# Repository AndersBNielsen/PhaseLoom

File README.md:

# PhaseLoom

PhaseLoom is a unique Software Defined Radio (SDR) frontend built around the legendary MOS Technology 6502 CPU, celebrating its 50th anniversary. This project combines classic computing with modern SDR techniques, offering a hands-on platform for radio experimentation and development.
Update: The PhaseLoom now has a companion ADC board with antialiasing filter, the [PhaseLatch Mini](https://github.com/AndersBNielsen/PhaseLatchMini)!

## Purchase

Interested in owning a PhaseLoom?  
[Buy one here](https://www.imania.dk/index.php?cPath=204&sort=5a&language=en).

## Project Story & Background
Hello everyone!
I just made the coolest gadget of the year. It’s a Software Defined Radio based on the MOS Technology 6502 CPU, which powered the Apple I & II, Commodore computers, NES, Ataris, and more. This year marks its 50th anniversary!

SDRs are the Swiss Army Knives of radio frequencies. Instead of purpose-built hardware for each use case, SDRs use software to handle filtering and demodulation, making them flexible and upgradable. With PhaseLoom, you get a 6502-based SDR platform—yes, a 6502 SDR!—that lets you experiment with radio signals, decode transponders, listen to shortwave, and more.

The PhaseLoom is designed as an Arduino-style shield for the 65uino, the smallest of my 6502-based computers. It features a Quadrature Sampling Detector, Phase Locked Loop LO Synthesizer, and SDR frontend. The project is open source, and all hardware files, schematics, and source code are available for you to use and modify.

## Features
- KiCad PCB and schematic files
- Gerber files for manufacturing
- Bill of Materials (BOM) and Component Placement List (CPL)
- Images of PCB versions and layouts
- Excel sheet for SI5351 PLL calculations
- Arduino shield form factor for easy integration
- Compatible with 6502, Arduino, ESP32, and other i2c-capable boards

## Technical Highlights
- Quadrature Sampling Detector using Tayloe-style commutating mixers
- SI5351 clock generator for flexible LO generation
- Differential signal processing for improved noise immunity
- Designed for direct conversion SDR and future expansion
- Open source 6502 assembly library for SI5351 control

## Folder Structure
- `PhaseLoom.kicad_pcb` / `PhaseLoom.kicad_sch`: Main PCB and schematic files
- `images/`: Photos and renders of PCB versions
- `jlcpcb/`: Manufacturing files for JLCPCB
  - `gerber/`: Gerber files for PCB fabrication
- `GRC/`: GNU Radio Companion flowgraphs
  - `Aliasing_example.grc`: Demonstrates aliasing effects and IQ sampling
  - `PhaseLoom.grc`: Flowgraph for PhaseLoom SDR frontend
- `PhaseLoom-backups/`: Backup archives of project versions
- `SI5351_PLL_Calc_Formulas.xlsx`: PLL calculation formulas

## How to Use
[6502 source code still lives over on the 65uino project](https://github.com/AndersBNielsen/65uino/)

The main 65uino firmware currently comes with support for the PhaseLoom built in. Assemble a recent binary and you're good to go. 

The 65uino automatically detects the si5351 and goes into SDR mode, that let's you use the buttons and LED's on the PhaseLoom to tune the channels. 

Leftmost button(1): Channel down
Second button: Unused
Third button: Unused
Fourth button: Channel up
Rightmost button: Tune to selected channel.

LED's show the current channel as a binary count. 

To change the available channels update the source code using the Excel spreadsheet to get new byte values for the lookup tables - let me know if you'd like to see a video about that. 

## Other host hardware?
Want to use the PhaseLoom with something that's not a 6502 computer? Go right ahead and use it with anything that does i2c - even better something that already has an si5351 library. 

## Images
Find PCB photos and renders in the `images/` folder for reference and documentation.

## Getting a PCB

## Production & Manufacturing
- The `jlcpcb/gerber/` folder contains all necessary files for PCB fabrication.
- The `production_files/` folder includes:
  - `BOM-PhaseLoom.csv`: Bill of Materials
  - `CPL-PhaseLoom.csv`: Component Placement List
  - `GERBER-PhaseLoom.zip`: Zipped Gerber files for easy upload

This project is kindly sponsored by JLCPCB. They offer cheap, professional looking PCBs and super fast delivery.

Step 1: Get the gerber file zip package from the /hardware folder

Step 2: Upload to JLCPCB [https://jlcpcb.com/?from=Anders_N](https://jlcpcb.com/?from=Anders_N)

Step 3: Pick your color, surface finish and order.

You can use these affiliate links to get a board for $2 and also get $54 worth of New User Coupons at: https://jlcpcb.com/?from=Anders_N

And in case you also want to order a 3D-printed case you can use this link. 
How to Get a $7 3D Printing Coupon: [https://3d.jlcpcb.com/?from=Anders3DP](https://jlc3dp.com/?from=Anders_N)

---

For more details, technical explanations, and the full story behind PhaseLoom, check out the project video and documentation. Special thanks to JLCPCB and Fnirsi for supporting the development of this project!

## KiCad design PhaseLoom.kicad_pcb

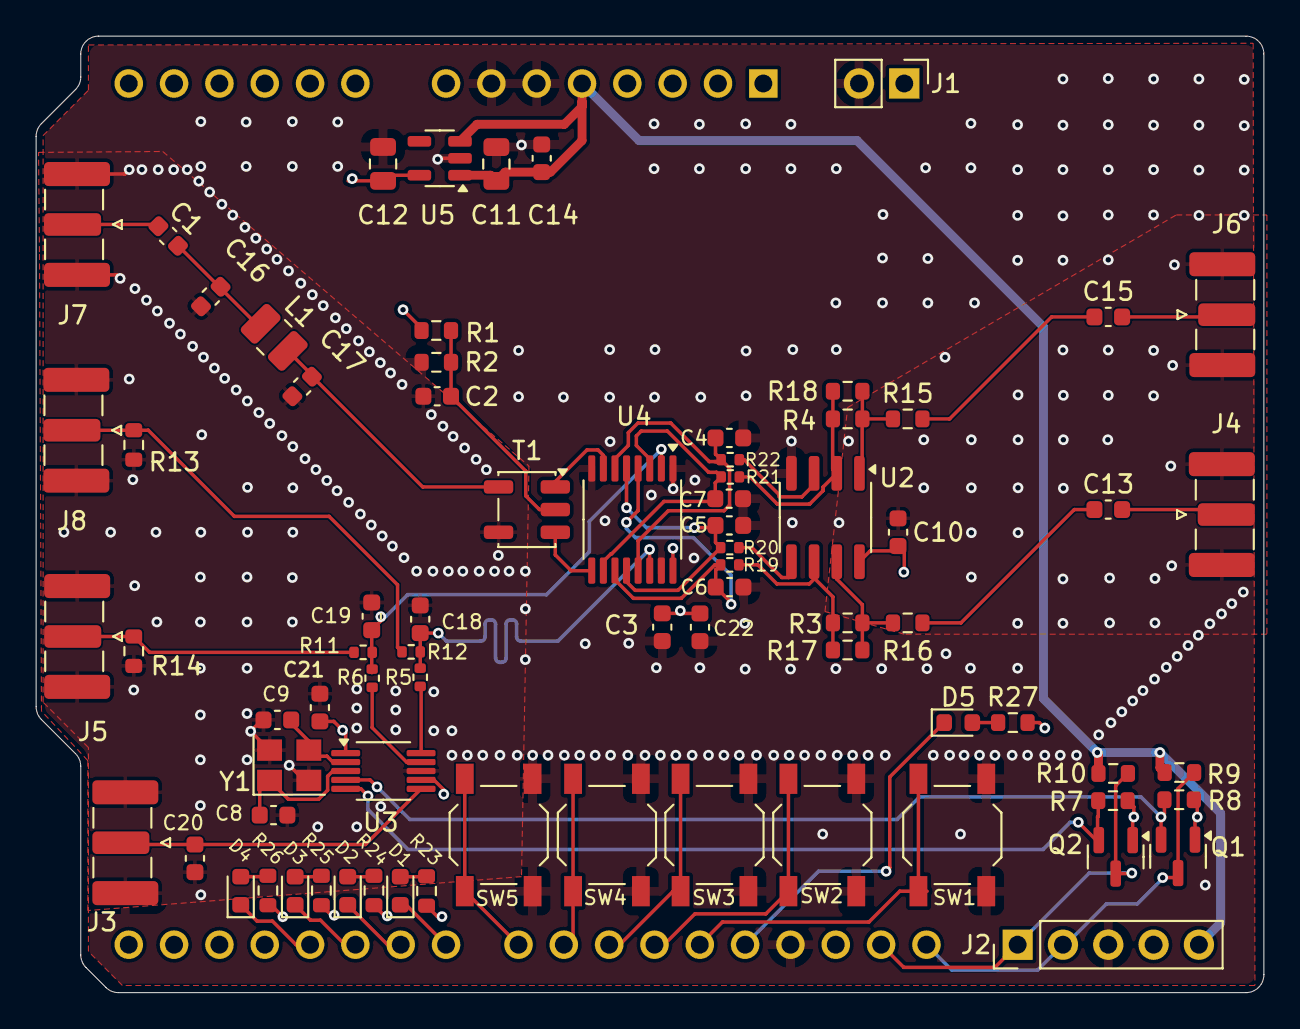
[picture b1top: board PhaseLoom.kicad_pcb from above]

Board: 4 copper layers, 68.8 x 53.6 mm, 77 parts (1 on the bottom side), 51 nets.

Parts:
A1: Arduino_UNO_R3
C1, C10, C21, C22: 100nF; C_0603_1608Metric
C2, C3, C13, C14, C15: 10uF; C_0603_1608Metric
C4, C5, C6, C7: 1nF; C_0603_1608Metric
C8, C9: 2pF; C_0603_1608Metric
C11, C12: 1uF; C_0805_2012Metric
C16, C17: 18pF; C_0603_1608Metric
C18, C19, C20: NC; C_0603_1608Metric
D1, D2, D3, D4, D5: RED; LED_0603_1608Metric
J1: NC; PinHeader_1x02_P2.54mm_Vertical
J2: NC; PinHeader_1x05_P2.54mm_Vertical
J3: CLK2; SMA_Samtec_SMA-J-P-H-ST-EM1_EdgeMount
J4: Q_OUT; SMA_Samtec_SMA-J-P-H-ST-EM1_EdgeMount
J5: LO_CLK; SMA_Samtec_SMA-J-P-H-ST-EM1_EdgeMount
J6: I_OUT; SMA_Samtec_SMA-J-P-H-ST-EM1_EdgeMount
J7: RF_IN; SMA_Samtec_SMA-J-P-H-ST-EM1_EdgeMount
J8: LO_CLK+90; SMA_Samtec_SMA-J-P-H-ST-EM1_EdgeMount
L1: 56nH; L_1008_2520Metric
Q1, Q2: AO3400A; SOT-23
R1, R2, R7, R8: 2k2; R_0603_1608Metric
R3, R4: 22k; R_0603_1608Metric
R5, R6, R11, R12, R19, R20, R21, R22: 0; R_0402_1005Metric
R9, R10, R13, R14, R17, R18: NC; R_0603_1608Metric
R15, R16: 49.9; R_0603_1608Metric
R23, R24, R25, R26, R27: 10k; R_0603_1608Metric
SW1: USR1; SW_SPST_TL3342
SW2: USR2; SW_SPST_TL3342
SW3: USR3; SW_SPST_TL3342
SW4: USR4; SW_SPST_TL3342
SW5: USR5; SW_SPST_TL3342
T1: 50:200; Transformer_MiniCircuits_AT224-1A
U2: ADA4891-2; SOIC-8_3.9x4.9mm_P1.27mm
U3: Si5351A-B-GTR; MSOP-10_3x3mm_P0.5mm
U4: 74CBTLV3253PW; TSSOP-16_4.4x5mm_P0.65mm
U5: MIC5504-3.3YM5; SOT-23-5
Y1: 25Mhz; Crystal_SMD_3225-4Pin_3.2x2.5mm

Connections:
+3V3: C3.1, C10.2, C12.1, C21.2, C22.2, J1.1, J2.4, Q1.1 (G), Q2.1 (G), R1.2, R7.2, R8.2, R23.2, R24.2, R25.2, R26.2, R27.2, U2.8 (V+), U3.1 (VDD), U3.7 (VDDO), U4.16 (VCC), U5.5 (VOUT)
+5V: A1.5 (+5V), C11.1, C14.1, J2.5, R9.2, R10.2, U5.1 (VIN), U5.3 (EN)
/CLK0: C18.1, R5.2, R12.1, U4.14 (S0)
/CLK1: C19.1, R6.2, R11.1, U4.2 (S1)
/I+: C4.2, R22.1, U4.6 (1B1), U4.13 (2B4)
/I-: C7.2, R21.1, U4.3 (1B4), U4.10 (2B1)
/Q+: C5.2, R20.1, U4.5 (1B2), U4.12 (2B3)
/Q-: C6.2, R19.1, U4.4 (1B3), U4.11 (2B2)
/RF+: T1.1 (SB), U4.7 (1A)
/RF-: T1.3 (SA), U4.9 (2A)
/SCL_5V: A1.32 (SCL/A5), J2.2, Q1.3 (D), R9.1
/SDA_5V: A1.31 (SDA/A4), J2.1, Q2.3 (D), R10.1
GND: A1.6 (GND), A1.7 (GND), A1.29 (GND), C2.2, C3.2, C4.1, C5.1, C6.1, C7.1, C8.2, C9.2, C10.1, C11.2, C12.2, C14.2, C16.1, C17.1, C18.2, C19.2, C20.2, C21.1, C22.1, J1.2, J2.3, J3.2 (Ext), J4.2 (Ext), J5.2 (Ext), J6.2 (Ext), J7.2 (Ext), J8.2 (Ext), R2.1, R13.1, R14.1, SW1.2, SW2.2, SW3.2, SW4.2, SW5.2, T1.4 (AB), U2.4 (V-), U3.8 (GND), U4.1 (1~OE), U4.8 (GND), U4.15 (2~OE), U5.2 (GND), Y1.2, Y1.4
unnamed: C1.2, C16.2, L1.1
unnamed: C13.1, R16.2
unnamed: C15.1, R15.2
unnamed: D1.2 (A), R23.1
unnamed: D2.2 (A), R24.1
unnamed: D3.2 (A), R25.1
unnamed: D4.2 (A), R26.1
unnamed: D5.2 (A), R27.1
unnamed: C20.1, J3.1 (In), U3.6 (CLK2)
unnamed: C13.2, J4.1 (In)
unnamed: J5.1 (In), R11.2, R14.2
unnamed: C15.2, J6.1 (In)
unnamed: C1.1, J7.1 (In)
unnamed: J8.1 (In), R12.2, R13.2
unnamed: Q1.2 (S), R8.1, U3.4 (SCL)
unnamed: Q2.2 (S), R7.1, U3.5 (SDA)
unnamed: R4.1, R15.1, R18.1, U2.1
unnamed: R3.1, R16.1, R17.1, U2.7
unnamed: C17.2, L1.2, T1.5 (AA)
unnamed: C2.1, R1.1, R2.2, T1.2 (SC)
unnamed: R22.2, U2.3 (+)
unnamed: R4.2, R18.2, R21.2, U2.2 (-)
unnamed: R20.2, U2.5 (+)
unnamed: R3.2, R17.2, R19.2, U2.6 (-)
unnamed: R5.1, U3.10 (CLK0)
unnamed: R6.1, U3.9 (CLK1)
unnamed: C9.1, U3.2 (XA), Y1.3
unnamed: C8.1, U3.3 (XB), Y1.1
USR1: A1.27 (D12), SW1.1
USR2: A1.26 (D11), SW2.1
USR3: A1.25 (D10), SW3.1
USR4: A1.24 (D9), SW4.1
USR5: A1.23 (D8), SW5.1
USRLED1: A1.19 (D4), D4.1 (K)
USRLED2: A1.20 (D5), D3.1 (K)
USRLED3: A1.21 (D6), D2.1 (K)
USRLED4: A1.22 (D7), D1.1 (K)
USRLED5: A1.28 (D13), D5.1 (K)

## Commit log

2025-07-28 v1.1 Fix: Swap I- and Q-, improve stitching
2025-09-05 Documentation and images
2025-09-06 Update docs
2025-09-08 GNURadio Flowgraphs
